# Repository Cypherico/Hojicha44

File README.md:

# Hojicha44

A low-profile wireless split keyboard with 44 keys, two knobs, and a gasket-mounted plate.

Set each half where your hands naturally land. The staggered columns follow your fingers, and four keys along each thumb’s arc put everyday controls within reach. Turn either knob for volume, scrolling, or track control, depending on the active layer. Push either one to mute.

[Find the v0.5.4 build files](pcb/MANUFACTURING.md) · [See the keymap](spec/keymap.md) · [Explore the v0.5.4 assembly](generated/renders/v0.5.4/bright/exploded.png) · [See all v0.5.4 renders](generated/renders/v0.5.4/README.md)

## What’s inside

- **Low-profile Choc v1 switches.** Hotswap sockets let you change the switches without soldering.
- **A floating polycarbonate plate.** PORON pads cradle the switch plate, and magnets hold each removable cover in place.
- **A wireless split.** Two nice!nano v2 controllers run ZMK and link the halves over Bluetooth. Connect to your computer over Bluetooth or plug into the left half for USB.
- **Familiar QWERTY with thumb layers.** Tap home-row keys for letters and hold them for modifiers. The thumb layers bring numbers, symbols, function keys, and navigation into reach. Choose a macOS or Windows/Linux keymap and put Space under either thumb.

## Build one

**v0.5.4 is the engineering sample.** Use the matching PCB, plate and case files from this tree. The diodes sit on the underside, so the switch plate can be through-cut from flat polycarbonate. The published v0.5.2 case can obstruct larger USB-C plugs at the low end of the socket stack. Build one pair and work through the first-article checks before ordering a batch. The PCB has a routed relief behind each debug jack so the plug boot can seat.

[Parts list](spec/bom.md) · [Fabrication guide](pcb/MANUFACTURING.md) · [First-article checklist](spec/first-article.md)

### v0.5.4 PCB, underside

[Left top](generated/renders/v0.5.4/pcb/Hojicha44-Left-top.png) · [Left bottom](generated/renders/v0.5.4/pcb/Hojicha44-Left-bottom.png) · [Right top](generated/renders/v0.5.4/pcb/Hojicha44-Right-top.png) · [Right bottom](generated/renders/v0.5.4/pcb/Hojicha44-Right-bottom.png)

The design files are available for anyone who wants to inspect or adapt the board. [KiCad projects](pcb/kicad/) · [Ergogen layout](layout/ergogen/config.yaml) · [Case design](case/)

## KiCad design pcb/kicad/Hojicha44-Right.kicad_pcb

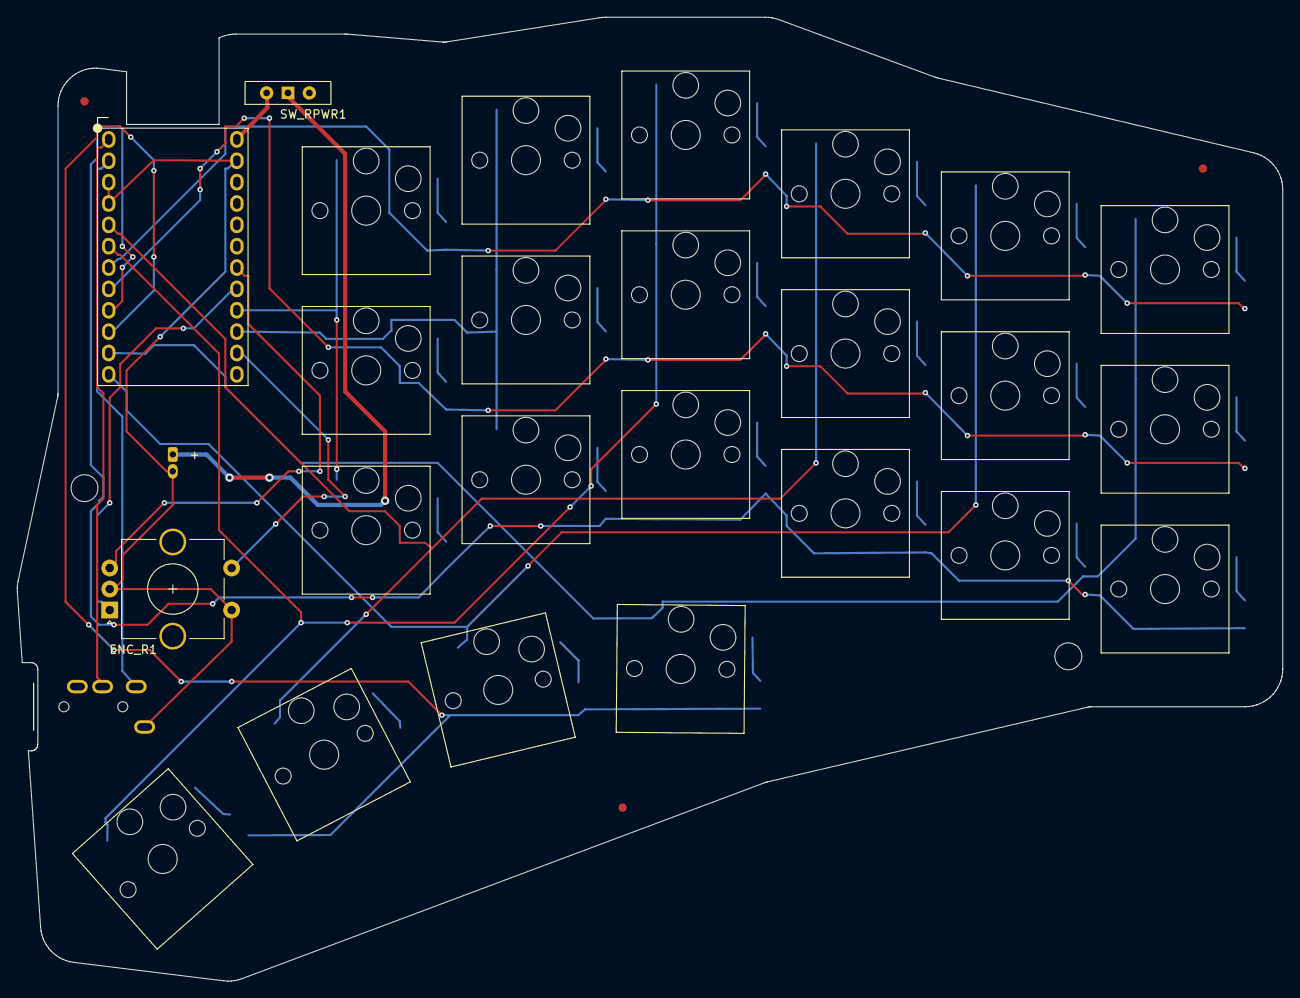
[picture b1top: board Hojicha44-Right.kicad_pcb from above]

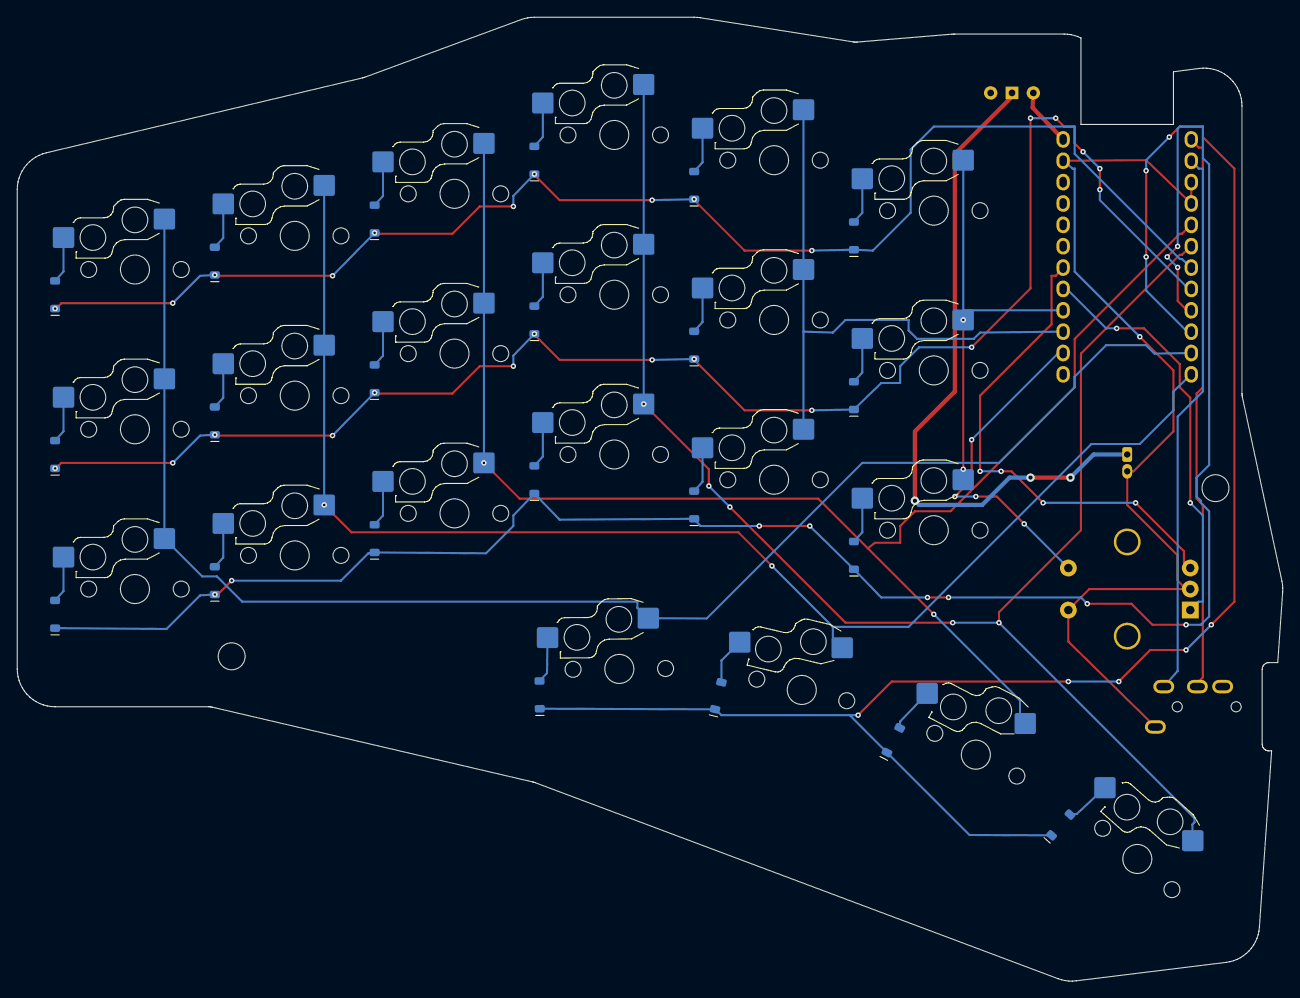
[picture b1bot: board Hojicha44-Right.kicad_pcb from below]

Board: 2 copper layers, 150.5 x 114.6 mm, 54 parts (22 on the bottom side), 40 nets.

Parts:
D_R00, D_R01, D_R02, D_R03, D_R04, D_R05, D_R06, D_R07, D_R08, D_R09, D_R10, D_R11, D_R12, D_R13, D_R14, D_R15, D_R16, D_R17, D_R18, D_R19, D_R20, D_R21: 1N4148W; D_SOD-123
ENC_R1: EC11E-Switch; RotaryEncoder_Alps_EC11E-Switch_Vertical_H20mm_CircularMoun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
FID_R1, FID_R2, FID_R3: FIDUCIAL; Fiducial_1mm_Mask3mm
J_R1: PJ-320A TRRS; TRRS-PJ-320A
J_R2: BATT_LIPO; JST_PH_S2B-PH-K_1x02_P2.00mm_Horizontal
MT_R1, MT_R2: TOOLING; MountingHole_3.2mm_M3
SW_R00: K00; SW_Hotswap_Kailh_Choc_V1_1.00u
SW_R01: K01; SW_Hotswap_Kailh_Choc_V1_1.00u
SW_R02: K02; SW_Hotswap_Kailh_Choc_V1_1.00u
SW_R03: K03; SW_Hotswap_Kailh_Choc_V1_1.00u
SW_R04: K04; SW_Hotswap_Kailh_Choc_V1_1.00u
SW_R05: K05; SW_Hotswap_Kailh_Choc_V1_1.00u
SW_R06: K06; SW_Hotswap_Kailh_Choc_V1_1.00u
SW_R07: K07; SW_Hotswap_Kailh_Choc_V1_1.00u
SW_R08: K08; SW_Hotswap_Kailh_Choc_V1_1.00u
SW_R09: K09; SW_Hotswap_Kailh_Choc_V1_1.00u
SW_R10: K10; SW_Hotswap_Kailh_Choc_V1_1.00u
SW_R11: K11; SW_Hotswap_Kailh_Choc_V1_1.00u
SW_R12: K12; SW_Hotswap_Kailh_Choc_V1_1.00u
SW_R13: K13; SW_Hotswap_Kailh_Choc_V1_1.00u
SW_R14: K14; SW_Hotswap_Kailh_Choc_V1_1.00u
SW_R15: K15; SW_Hotswap_Kailh_Choc_V1_1.00u
SW_R16: K16; SW_Hotswap_Kailh_Choc_V1_1.00u
SW_R17: K17; SW_Hotswap_Kailh_Choc_V1_1.00u
SW_R18: K18; SW_Hotswap_Kailh_Choc_V1_1.00u
SW_R19: K19; SW_Hotswap_Kailh_Choc_V1_1.00u
SW_R20: K20; SW_Hotswap_Kailh_Choc_V1_1.00u
SW_R21: K21; SW_Hotswap_Kailh_Choc_V1_1.00u
SW_RPWR1: PWR_SW; SW_Slide-03_Wuerth-WS-SLTV_10x2.5x6.4_P2.54mm
U_R1: nice!nano v2; Socket_Strips_2x12_P2.54mm_NiceNano

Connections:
/COL0_R: SW_R00.1, SW_R06.1, SW_R12.1, SW_R18.1, U_R1.11
/COL1_R: SW_R01.1, SW_R07.1, SW_R13.1, SW_R19.1, U_R1.12
/COL2_R: SW_R02.1, SW_R08.1, SW_R14.1, SW_R20.1, U_R1.5
/COL3_R: SW_R03.1, SW_R09.1, SW_R15.1, SW_R21.1, U_R1.6
/COL4_R: SW_R04.1, SW_R10.1, SW_R16.1, U_R1.15
/COL5_R: SW_R05.1, SW_R11.1, SW_R17.1, U_R1.16
/ENC_A_R: ENC_R1.A, U_R1.17
/ENC_B_R: ENC_R1.B, U_R1.18
/ENC_SW_R: ENC_R1.S1, U_R1.14
/ROW0_R: D_R00.1, D_R01.1, D_R02.1, D_R03.1, D_R04.1, D_R05.1, U_R1.7
/ROW1_R: D_R06.1, D_R07.1, D_R08.1, D_R09.1, D_R10.1, D_R11.1, U_R1.8
/ROW2_R: D_R12.1, D_R13.1, D_R14.1, D_R15.1, D_R16.1, D_R17.1, U_R1.9
/ROW3_R: D_R18.1, D_R19.1, D_R20.1, D_R21.1, U_R1.10
/TRRS_R1: J_R1.R1, U_R1.1
/TRRS_T: J_R1.T, U_R1.2
/VBAT_SW_R: SW_RPWR1.2, U_R1.24
GND: ENC_R1.C, ENC_R1.S2, J_R1.S, J_R2.2, U_R1.3, U_R1.4, U_R1.23
unnamed: D_R00.2, SW_R00.2
unnamed: D_R01.2, SW_R01.2
unnamed: D_R02.2, SW_R02.2
unnamed: D_R03.2, SW_R03.2
unnamed: D_R04.2, SW_R04.2
unnamed: D_R05.2, SW_R05.2
unnamed: D_R06.2, SW_R06.2
unnamed: D_R07.2, SW_R07.2
unnamed: D_R08.2, SW_R08.2
unnamed: D_R09.2, SW_R09.2
unnamed: D_R10.2, SW_R10.2
unnamed: D_R11.2, SW_R11.2
unnamed: D_R12.2, SW_R12.2
unnamed: D_R13.2, SW_R13.2
unnamed: D_R14.2, SW_R14.2
unnamed: D_R15.2, SW_R15.2
unnamed: D_R16.2, SW_R16.2
unnamed: D_R17.2, SW_R17.2
unnamed: D_R18.2, SW_R18.2
unnamed: D_R19.2, SW_R19.2
unnamed: D_R20.2, SW_R20.2
unnamed: D_R21.2, SW_R21.2
unnamed: J_R2.1, SW_RPWR1.1
